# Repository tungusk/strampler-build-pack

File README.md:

# Strämpler Build Pack

Everything you need to **build your own [CTAG Strämpler](https://github.com/ctag-fh-kiel/ctag-straempler)** —
the open-source ESP32 eurorack sample-streaming module — in its compact
**18 HP Antumbra redesign**. Board files in both Eagle *and* KiCad, complete
BOMs with 2026 sourcing fixes, a ready-to-upload fab/assembly package, and
per-kit ordering guides.

## Why this repo exists

The original design files live inside the firmware repo and are in **Eagle
format — a dead tool** (Autodesk sunset Eagle in 2026). The ready-made
panel/PCB sets that used to be sold are delisted. Several key parts of the
2019 BOM have gone EOL. This pack collects the originals, converts them to
a living format, and documents what it actually takes to build one today.

## What's here

| Path | Contents |
|---|---|
| `hardware-eagle/` | The designer's original Eagle 7.3 files: main board + schematic + FR4 panel (untouched) |
| `hardware-kicad/` | **KiCad 10 conversion** — full linked project (schematic + board + symbol lib), converted panel, 3D verification renders, schematic PDF |
| `bom/` | Official Antumbra BOM (Mouser refs), a schematic-derived cross-check BOM, a **Mouser BOM-tool upload file for one kit**, the non-Mouser parts list, and the CTAG RevD reference BOM |
| `assembly-pcbway/` | Ready-to-upload turnkey assembly package: fab BOM, pick-and-place (CPL), order guide, price estimate |
| `KIT-GUIDE.md` | Ordering bare boards + parts as DIY kits, per-kit costs, build order, licensing |
| `KNOB-OPTIONS-20260911.md` | Knob-cap shopping: what is fitted, the panel's 19.27 mm row gap that caps knob diameter, and the Thonk / AliExpress options screened against it |

## 2026 sourcing notes (the important bits)

- **WM8731 codec: obsolete.** Broker stock only (Rochester Electronics for
  genuine EOL parts). The assembly package marks it DNP for hand-soldering.
- **ESP32-WROVER-B: NRND** → use **ESP32-WROVER-IE** (the **-I**/IPEX
  external-antenna variant is required — the module lives behind a metal panel).
- Jacks/pots/SD from [Thonk](https://thonk.co.uk); TFT + antenna from AliExpress.
- Rough costs: **~$160–195/kit** DIY, **~$350–420** for a fab-assembled build.
  Details in `KIT-GUIDE.md` and `assembly-pcbway/PRICE-ESTIMATE.md`.

## Firmware

- Upstream: [ctag-fh-kiel/ctag-straempler](https://github.com/ctag-fh-kiel/ctag-straempler) (GPL 3.0)
- Extended fork with the multi-machine firmware (drum sampler, looper,
  slicer, granular, glitch, Freesound browser, web teleremote):
  [tungusk/ctag-straempler](https://github.com/tungusk/ctag-straempler), branch `v09-machines`
- Flash with `--flash_size detect`; see the firmware repos for build docs.

## Licensing — read before selling anything

- **Hardware: CC BY-NC-SA 4.0** (unchanged from upstream — see `LICENSE.md`).
  Build for yourself, share these files, remix them: all encouraged.
  **Selling boards/kits/modules requires permission** from the rights
  holders (CTAG and Antumbra). Modifications you distribute must carry the
  same license.
- **Firmware: GPL 3.0** — commercial use allowed with source provision.

## Provenance & changes

Original design © 2019 Robert Manzke, Phillip Lamp, Niklas Wantrupp
([CTAG, Kiel UAS](https://www.creative-technologies.de)); PCB redesign by
David Szebenyi ([Antumbra](https://antumbra.eu)). This pack adds (2026-07,
CC BY-NC-SA 4.0): the KiCad 10.0.4 conversion (`kicad-cli pcb import` for the
boards, GUI Eagle-project import for the schematic; auto-matched layers,
KiCad layer names), generated CPL and fab BOMs, the Mouser kit BOM with EOL
substitutions, verification renders/PDF, and the ordering/cost documentation.
Not affiliated with or endorsed by CTAG or Antumbra — errors are ours, not
theirs. Verify footprints against the Eagle originals before fabbing
modified boards.

## Experimental: E-mu-format panel (2026-09)

`panel-emu/` — a 6" × 6" E-mu Modular style front panel for the main board
with 1/4" Switchcraft jacks, bus-normalled CV/trigger inputs, and a ±12 V
regulator sub-board for the E-mu ±15 V bus. Parametric generator + SVG/DXF
cut and art files + README (BOM, wiring, E-mu conventions). One-off for a
hackerspace system; slow burn.

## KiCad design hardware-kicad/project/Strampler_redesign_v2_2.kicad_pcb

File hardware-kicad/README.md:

# Editing the boards (KiCad 10+)

- **Main board + schematic**: open `project/Strampler_redesign_v2_2.kicad_pro`
  — a full linked project (schematic, board, and the Eagle-imported symbol
  library). Footprints are embedded in the board, so it is self-contained.
- **Panel**: open `strampler_panel_v2_2.kicad_pcb` directly in the PCB
  Editor. The artwork is ~34k filled polygons on F.Silkscreen; the copper
  pours are filled zones. It is heavy but edits fine.

After editing, regenerate all fab outputs (gerber zips + centroid) with:

```
./make-fab-files.sh
```

Both gerber sets passed PCBWay audit (2026-07) as generated by that script's
commands.

## Provenance & pitfalls

These files were converted from the Eagle 7.3 originals (`../hardware-eagle/`)
with KiCad 10.0.4. Two importer pitfalls are already fixed here — beware if
you ever re-import from Eagle instead of editing these files:

1. The importer creates **unfilled zones**, which plot as EMPTY gerber
   layers (missing copper, mask and artwork). Fixed by filling copper zones
   and converting non-copper zones to filled `gr_poly` shapes.
2. The importer maps Eagle's t/bRestrict layers to layer `"UNDEFINED"`,
   which KiCad's own parser then refuses to load. The first fix remapped
   them to `User.1` — **which was itself a bug**: `User.1` is not a copper
   layer, so the 1876 tiny restrict rectangles did nothing and the copper
   pours filled straight under the LED light window. The 2026-07 panel run
   came back with a **copper wave** where the original has bare FR4 (found
   2026-08-28 at first-module assembly). **Fixed 2026-08-28:** the 938
   unique rectangles (identical to the F/B.Mask window polygons) were merged
   into one polygon and replaced by a single **keep-out rule area on
   F.Cu + B.Cu** (`copperpour not_allowed`, named "LED light window");
   zones refilled; panel gerbers regenerated. Verified: filled copper ∩
   window = 0 on both layers.

## Main-board audit (2026-08-28) — keep-outs OK, one mask sliver restored

After the panel bug, the main board was checked for the same class of
loss. Eagle's `tRestrict`/`bRestrict` circles (mounting holes of P3 TFT,
jacks, PCB screws) and the `vRestrict` under the crystal all survived as
proper rule areas inside the footprints (`copperpour not_allowed` on
F.Cu/B.Cu; via keep-out on both). Verified with pcbnew: filled copper ∩
every keep-out = 0 (64 pairs). The only dropped item was a 0.15 × 1.3 mm
`tStop` sliver in the `SJ` (solder jumper) package — the mask opening
between SJ1's two pads that makes it bridgeable. Restored as an `fp_rect`
on B.Mask (SJ1 is on the bottom); main gerbers regenerated. The fabbed
2026-07 main boards lack that sliver: SJ1 can still be bridged, it just
takes a blob over the ~0.1 mm mask web. SJ1 joins ESP32 IO19 to TFT
connector pin 9.

## Panel v2_3 (2026-08-29) — M7 pot holes

`strampler_panel_v2_3.kicad_pcb` is the current panel: v2_2 plus the four
CV pot holes and POT1's hole resized 9.2/8.2 → 7.2 mm for M7-bushing pots
(Same Sky PTN091/PTN092 — see build-pack COMPLETION-SHOPPING §POT2–5).
The other 8.2 mm hole is the ENCODER's — deliberately unchanged.
`make-fab-files.sh` builds v2_3; v2_2 is kept as the pre-M7 version
matching the five fabbed (LED-window-defective) panels.

## Refilling zones from the command line

`kicad-cli` has no zone-fill command. After editing a board outside the
GUI (e.g. scripted changes), refill with the bundled Python before
running `make-fab-files.sh`:

```
PY=~/Applications/KiCad/KiCad.app/Contents/Frameworks/Python.framework/Versions/Current/bin/python3
$PY -c "import pcbnew; b=pcbnew.LoadBoard('strampler_panel_v2_2.kicad_pcb'); \
  pcbnew.ZONE_FILLER(b).Fill(b.Zones()); pcbnew.SaveBoard('strampler_panel_v2_2.kicad_pcb', b)"
```

(`SaveBoard` drops a stray `.kicad_pro` next to the panel — delete it.)

Verify against the Eagle originals and the `render-main-*.png` references
before fabbing modified boards. License: CC BY-NC-SA 4.0 (see ../LICENSE.md).

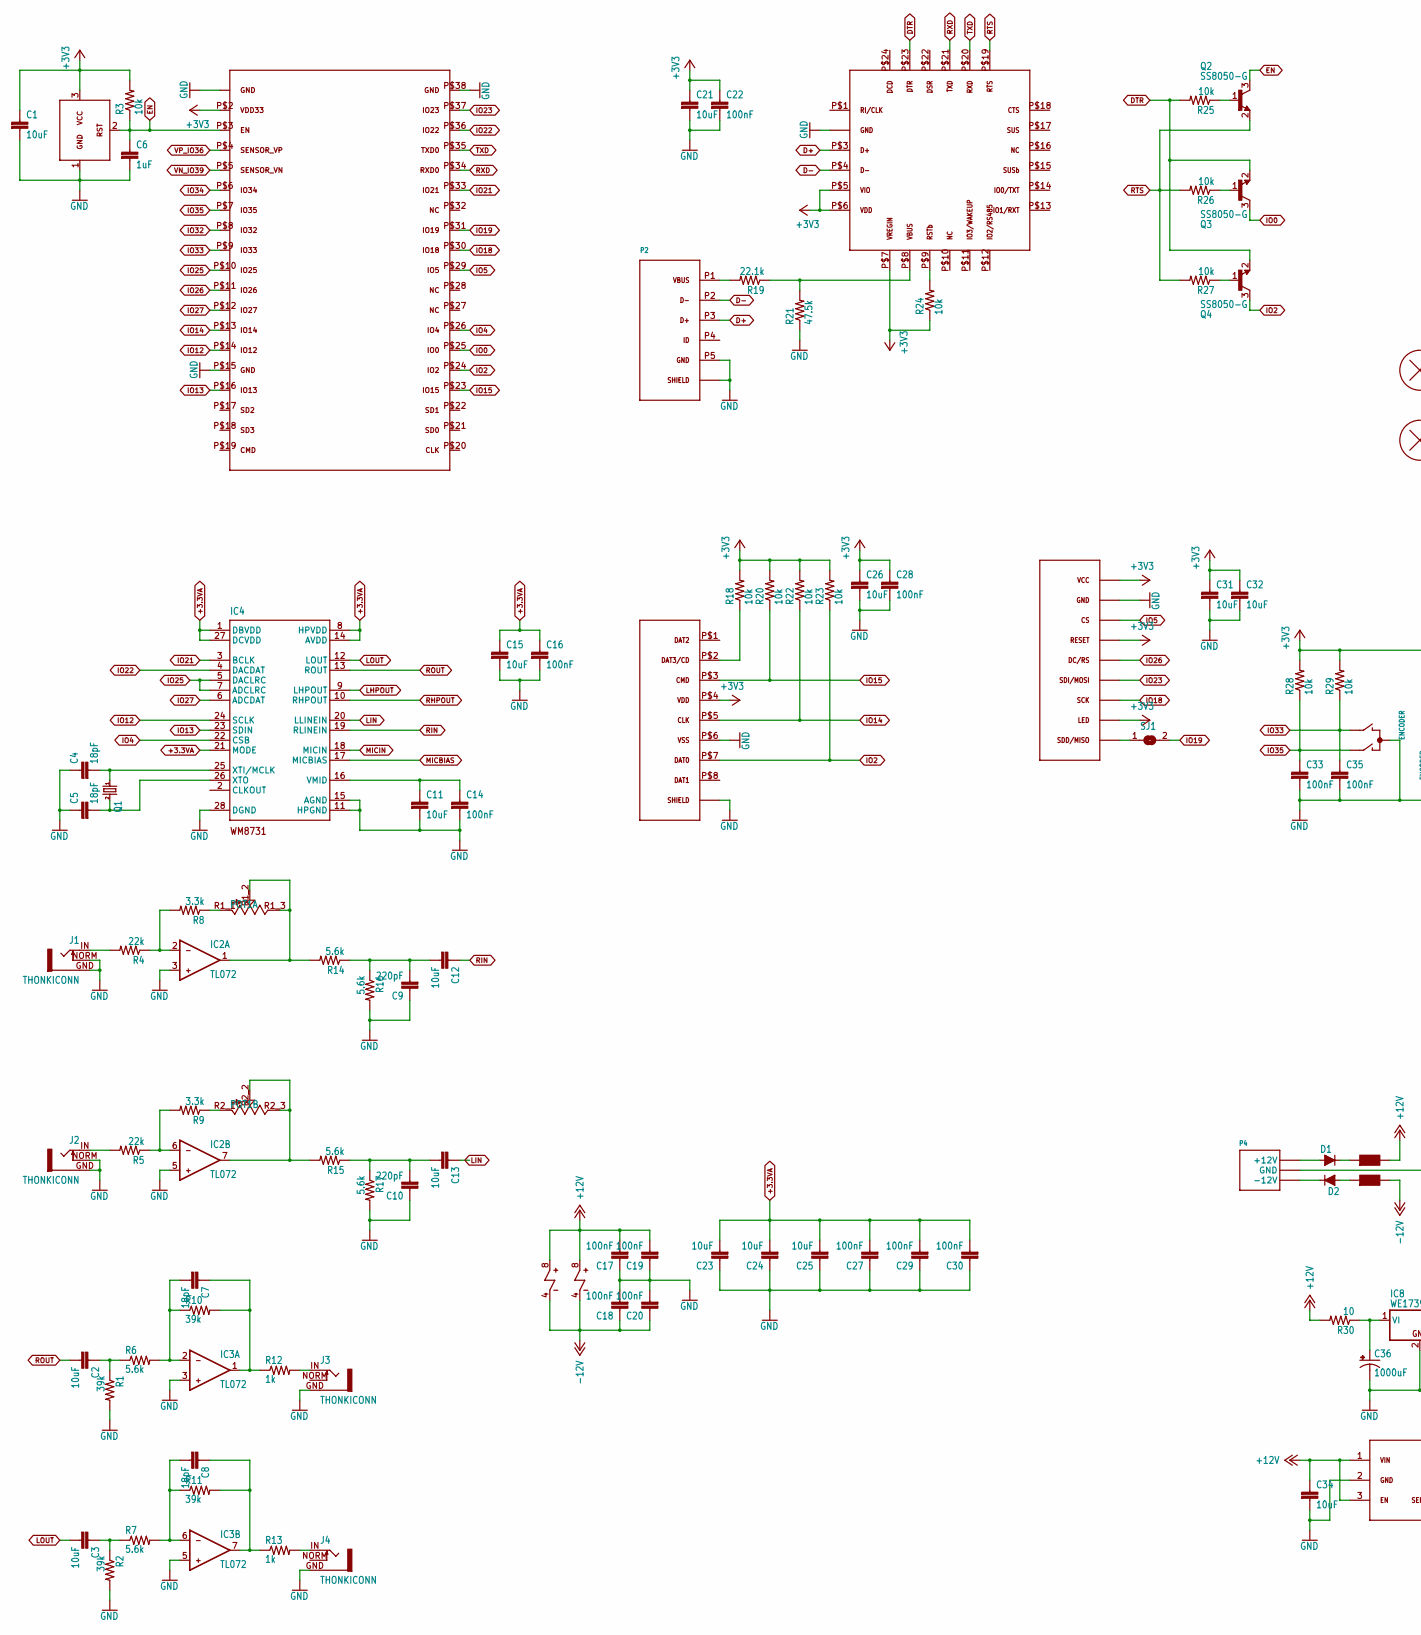
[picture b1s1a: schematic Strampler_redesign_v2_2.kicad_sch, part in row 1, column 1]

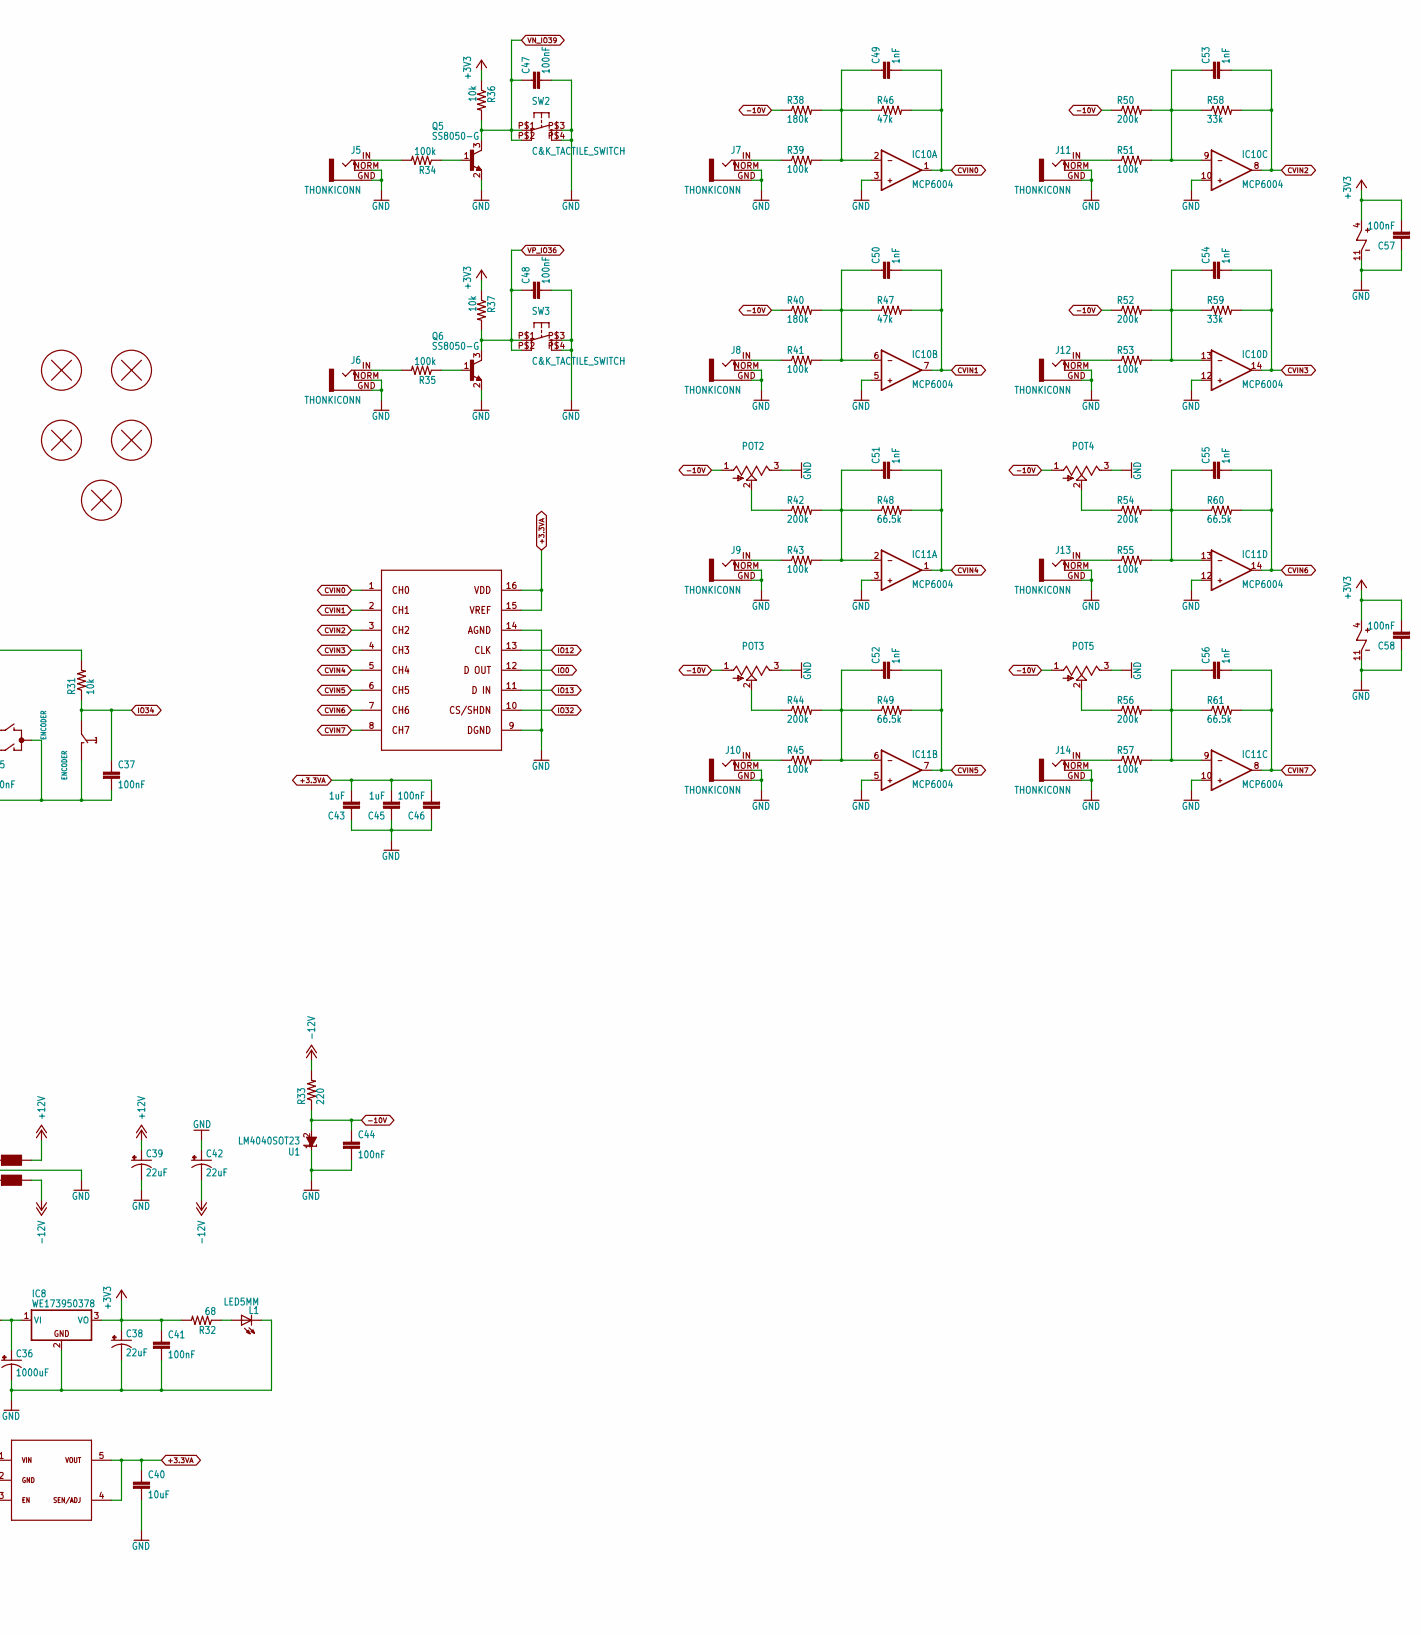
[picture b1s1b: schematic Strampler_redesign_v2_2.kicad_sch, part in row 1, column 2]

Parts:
C1, C2, C3, C11, C12, C13, C15, C21, C23, C24, C25, C26, C31, C32, C40: 10uF; R0805
C4, C5, C7, C8: 18pF; RESISTOR_0603
C6, C43, C45: 1uF; RESISTOR_0603
C9, C10: 220pF; RESISTOR_0603
C14, C16, C17, C18, C19, C20, C22, C27, C28, C29, C30, C33, C35, C37, C41, C44, C46, C47, C48, C57, C58: 100nF; RESISTOR_0603
C34: 10uF; R1210
C36: 1000uF; PANASONIC_G
C38, C39, C42: 22uF; 1206_POL
C49, C50, C51, C52, C53, C54, C55, C56: 1nF; RESISTOR_0603
D1, D2: DIODE; SOD123
F1, F2: FERRITE-BEAD0805; R0805
H1, H2, H3, H4, H5: PCB_SCREW
IC1: MIC803; SOT23
IC2, IC3: TL072; SOIC8
IC4: WM8731; SSOP28
IC5: ESP32-WROVER-B
IC6: CP2102N
IC7: ADP7118; SOT23-5L
IC8: WE173950378; WE78
IC9: MCP3208; SOIC16
IC10, IC11: MCP6004; TSSOP14
J1, J2, J3, J4, J5, J6, J7, J8, J9, J10, J11, J12, J13, J14: THONKICONN; PROTOJACK
L1: LED5MM; LED_5MM
P1: SD-CARD; SD-CARD-THONK
P2: USB-B; USB-B-MOLEX-1050170001
P3: MSP2202_DISPLAY
P4: POWER_SIMPLE10; POWER_10
POT1: POT_DUAL_THONK
POT2, POT3, POT4, POT5: POT_VERTICAL; ALPS_POT_VERTICAL
Q1: CRYSTAL; HC49UP
Q2, Q3, Q4, Q5, Q6: SS8050-G; SOT23
R1, R2, R10, R11: 39k; RESISTOR_0603
R3, R18, R20, R22, R23, R24, R25, R26, R27, R28, R29, R31, R36, R37: 10k; RESISTOR_0603
R4, R5: 22k; RESISTOR_0603
R6, R7, R14, R15, R16, R17: 5.6k; RESISTOR_0603
R8, R9: 3.3k; RESISTOR_0603
R12, R13: 1k; RESISTOR_0603
R19: 22.1k; RESISTOR_0603
R21: 47.5k; RESISTOR_0603
R30: 10; R2512
R32: 68; RESISTOR_0603
R33: 220; RESISTOR_0603
R34, R35, R39, R41, R43, R45, R51, R53, R55, R57: 100k; RESISTOR_0603
R38, R40: 180k; RESISTOR_0603
R42, R44, R50, R52, R54, R56: 200k; RESISTOR_0603
R46, R47: 47k; RESISTOR_0603
R48, R49, R60, R61: 66.5k; RESISTOR_0603
R58, R59: 33k; RESISTOR_0603
SJ1: SJ
SW1: ENCODER; ALPS_EC12E_SW; MPN EC12E2424407
SW2, SW3: C&K_TACTILE_SWITCH
U1: LM4040SOT23; SOT23

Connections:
+3.3VA: C15.1, C16.1, C23.2, C24.2, C25.2, C27.2, C29.2, C30.2, C40.1, C43.2, C45.2, C46.2, IC4.1 (DBVDD), IC4.8 (HPVDD), IC4.14 (AVDD), IC4.21 (MODE), IC4.27 (DCVDD), IC7.4, IC7.5, IC9.15, IC9.16
+3V3: C1.1, C21.1, C22.1, C26.1, C28.1, C31.1, C32.1, C38.2 (+), C41.1, C57.2, C58.2, IC1.3, IC5.P$2, IC6.P$5, IC6.P$6, IC6.P$7, IC8.3 (VO), IC10.4, IC11.4, P1.P$4, P3.LED, P3.LED1, P3.RESET, P3.RESET1, P3.VCC, P3.VCC1, R3.2, R18.2, R20.2, R22.2, R23.2, R24.1, R28.2, R29.2, R31.2, R32.2, R36.1, R37.1
+12V: C17.2, C19.2, C34.1, C39.2 (+), F1.1, IC2.8, IC3.8, IC7.1, IC7.3, R30.2
-10V: C44.1, POT2.1 (A), POT3.1 (A), POT4.1 (A), POT5.1 (A), R33.1, R38.1, R40.1, R50.1, R52.1, U1.2 (A)
-12V: C18.1, C20.1, C42.1 (-), F2.1, IC2.4, IC3.4, R33.2
CVIN0: C49.2, IC9.1, IC10.1, R46.2
CVIN1: C50.2, IC9.2, IC10.7, R47.2
CVIN2: C53.2, IC9.3, IC10.8, R58.2
CVIN3: C54.2, IC9.4, IC10.14, R59.2
CVIN4: C51.2, IC9.5, IC11.1, R48.2
CVIN5: C52.2, IC9.6, IC11.7, R49.2
CVIN6: C55.2, IC9.7, IC11.14, R60.2
CVIN7: C56.2, IC9.8, IC11.8, R61.2
D+: IC6.P$3, P2.P3
D-: IC6.P$4, P2.P2
DTR: IC6.P$23, Q3.2 (E), Q4.2 (E), R25.2
EN: C6.1, IC1.2, IC5.P$3, Q2.3 (C), R3.1
GND: C1.2, C4.1, C5.1, C6.2, C9.1, C10.1, C11.2, C14.2, C15.2, C16.2, C17.1, C18.2, C19.1, C20.2, C21.2, C22.2, C23.1, C24.1, C25.1, C26.2, C27.1, C28.2, C29.1, C30.1, C31.2, C32.2, C33.2, C34.2, C35.2, C36.-, C37.2, C38.1 (-), C39.1 (-), C40.2, C41.2, C42.2 (+), C43.1, C44.2, C45.1, C46.1, C47.2, C48.2, C57.1, C58.1, IC1.1, IC2.3, IC2.5, IC3.3, IC3.5, IC4.11 (HPGND), IC4.15 (AGND), IC4.28 (DGND), IC5.GND, IC5.GND2, IC5.P$1, IC5.P$15, IC5.P$38, IC6.GND, IC6.GND2, IC6.P$2, IC7.2, IC8.2 (GND), IC9.9, IC9.14, IC10.3, IC10.5, IC10.10, IC10.11, IC10.12, IC11.3, IC11.5, IC11.10, IC11.11, IC11.12, J1.GND, J1.NORM, J2.GND, J2.NORM, J3.GND, J4.GND, J5.GND, J5.NORM, J6.GND, J6.NORM, J7.GND, J7.NORM, J8.GND, J8.NORM, J9.GND, J9.NORM, J10.GND, J10.NORM, J11.GND, J11.NORM, J12.GND, J12.NORM, J13.GND, J13.NORM, J14.GND, J14.NORM, L1.K (C), P1.P$6, P1.P$9, P1.P$10, P2.P5, P2.P$1, P2.P$2, P2.P$8, P2.P$9, P2.P$10, P2.P$11, P3.GND, P3.GND1, P4.3 (GND), P4.4 (GND), P4.5 (GND), P4.6 (GND), P4.7 (GND), P4.8 (GND), POT2.3 (B), POT3.3 (B), POT4.3 (B), POT5.3 (B), Q5.2 (E), Q6.2 (E), R1.2, R2.2, R16.2, R17.2, R21.1, SW1.C, SW1.D (1), SW2.P$3 (3), SW2.P$4 (4), SW3.P$3 (3), SW3.P$4 (4), U1.1 (C)
IO0: IC5.P$25, IC9.12, Q3.3 (C)
IO2: IC5.P$24, P1.P$7, Q4.3 (C), R23.1
IO4: IC4.22 (CSB), IC5.P$26
IO5: IC5.P$29, P3.CS, P3.CS1
IO12: IC4.24 (SCLK), IC5.P$14, IC9.13
IO13: IC4.23 (SDIN), IC5.P$16, IC9.11
IO14: IC5.P$13, P1.P$5, R22.1
IO15: IC5.P$23, P1.P$3, R20.1
IO18: IC5.P$30, P3.SCK, P3.SCK1
IO19: IC5.P$31, SJ1.2
IO21: IC4.3 (BCLK), IC5.P$33
IO22: IC4.4 (DACDAT), IC5.P$36
IO23: IC5.P$37, P3.SDI/MOSI, P3.SDI/MOSI1
IO25: IC4.5 (DACLRC), IC4.7 (ADCLRC), IC5.P$10
IO26: IC5.P$11, P3.DC/RS, P3.DC/RS1
IO27: IC4.6 (ADCDAT), IC5.P$12
IO32: IC5.P$8, IC9.10
IO33: C35.1, IC5.P$9, R29.1, SW1.B
IO34: C37.1, IC5.P$6, R31.1, SW1.E (2)
IO35: C33.1, IC5.P$7, R28.1, SW1.A
LHPOUT: IC4.9 (LHPOUT)
LIN: C13.1, IC4.20 (LLINEIN)
LOUT: C3.2, IC4.12 (LOUT)
MICBIAS: IC4.17 (MICBIAS)
MICIN: IC4.18 (MICIN)
unnamed: IC6.P$9, R24.2
unnamed: IC6.P$8, R19.1, R21.2
unnamed: Q2.1 (B), R25.1
unnamed: P2.P1, R19.2
unnamed: P1.P$2, R18.1
unnamed: Q3.1 (B), R26.1
unnamed: P3.SDD/MISO, P3.SDD/MISO1, SJ1.1
unnamed: J5.IN, R34.2
unnamed: Q4.1 (B), R27.1
unnamed: J6.IN, R35.2
unnamed: Q5.1 (B), R34.1
unnamed: Q6.1 (B), R35.1
unnamed: J7.IN, R39.1
unnamed: J11.IN, R51.1
unnamed: C53.1, IC10.9, R50.2, R51.2, R58.1
unnamed: J8.IN, R41.1
unnamed: C49.1, IC10.2, R38.2, R39.2, R46.1
unnamed: POT3.2 (W), R44.1
unnamed: C50.1, IC10.6, R40.2, R41.2, R47.1
unnamed: J12.IN, R53.1
unnamed: C54.1, IC10.13, R52.2, R53.2, R59.1
unnamed: POT2.2 (W), R42.1
unnamed: J9.IN, R43.1
unnamed: C51.1, IC11.2, R42.2, R43.2, R48.1
unnamed: J13.IN, R55.1
unnamed: C55.1, IC11.13, R54.2, R55.2, R60.1
unnamed: J10.IN, R45.1
unnamed: C52.1, IC11.6, R44.2, R45.2, R49.1
unnamed: J14.IN, R57.1
unnamed: C56.1, IC11.9, R56.2, R57.2, R61.1
unnamed: J1.IN, R4.2
unnamed: IC2.2, R4.1, R8.2
unnamed: D1.+, P4.9 (+12V), P4.10 (+12V)
unnamed: POT1.R1_1 (A), R8.1
unnamed: POT5.2 (W), R56.1
unnamed: IC2.1, POT1.R1_2 (W), POT1.R1_3 (B), R14.2
unnamed: C9.2, C12.2, R14.1, R16.1
unnamed: POT4.2 (W), R54.1
unnamed: J2.IN, R5.2
unnamed: IC2.6, R5.1, R9.2
unnamed: POT1.R2_1 (A), R9.1
unnamed: IC2.7, POT1.R2_2 (W), POT1.R2_3 (B), R15.2
unnamed: C5.2, IC4.26 (XTO), Q1.2
unnamed: C4.2, IC4.25 (XTI/MCLK), Q1.1
unnamed: C10.2, C13.2, R15.1, R17.1
unnamed: C7.1, IC3.1, R10.2, R12.1
unnamed: D1.-, F1.2
unnamed: C7.2, IC3.2, R6.2, R10.1
unnamed: C2.1, R1.1, R6.1
unnamed: C36.+, IC8.1 (VI), R30.1
unnamed: J3.IN, R12.2
unnamed: D2.-, P4.1 (-12V), P4.2 (-12V)
unnamed: C8.1, IC3.7, R11.2, R13.1
unnamed: C8.2, IC3.6, R7.2, R11.1
unnamed: C11.1, C14.1, IC4.16 (VMID)
unnamed: C3.1, R2.1, R7.1
unnamed: J4.IN, R13.2
unnamed: D2.+, F2.2
unnamed: L1.A, R32.1
RHPOUT: IC4.10 (RHPOUT)
RIN: C12.1, IC4.19 (RLINEIN)
ROUT: C2.2, IC4.13 (ROUT)
RTS: IC6.P$19, Q2.2 (E), R26.2, R27.2
RXD: IC5.P$34, IC6.P$21
TXD: IC5.P$35, IC6.P$20
VN_IO39: C47.1, IC5.P$5, Q5.3 (C), R36.2, SW2.P$1 (1), SW2.P$2 (2)
VP_IO36: C48.1, IC5.P$4, Q6.3 (C), R37.2, SW3.P$1 (1), SW3.P$2 (2)

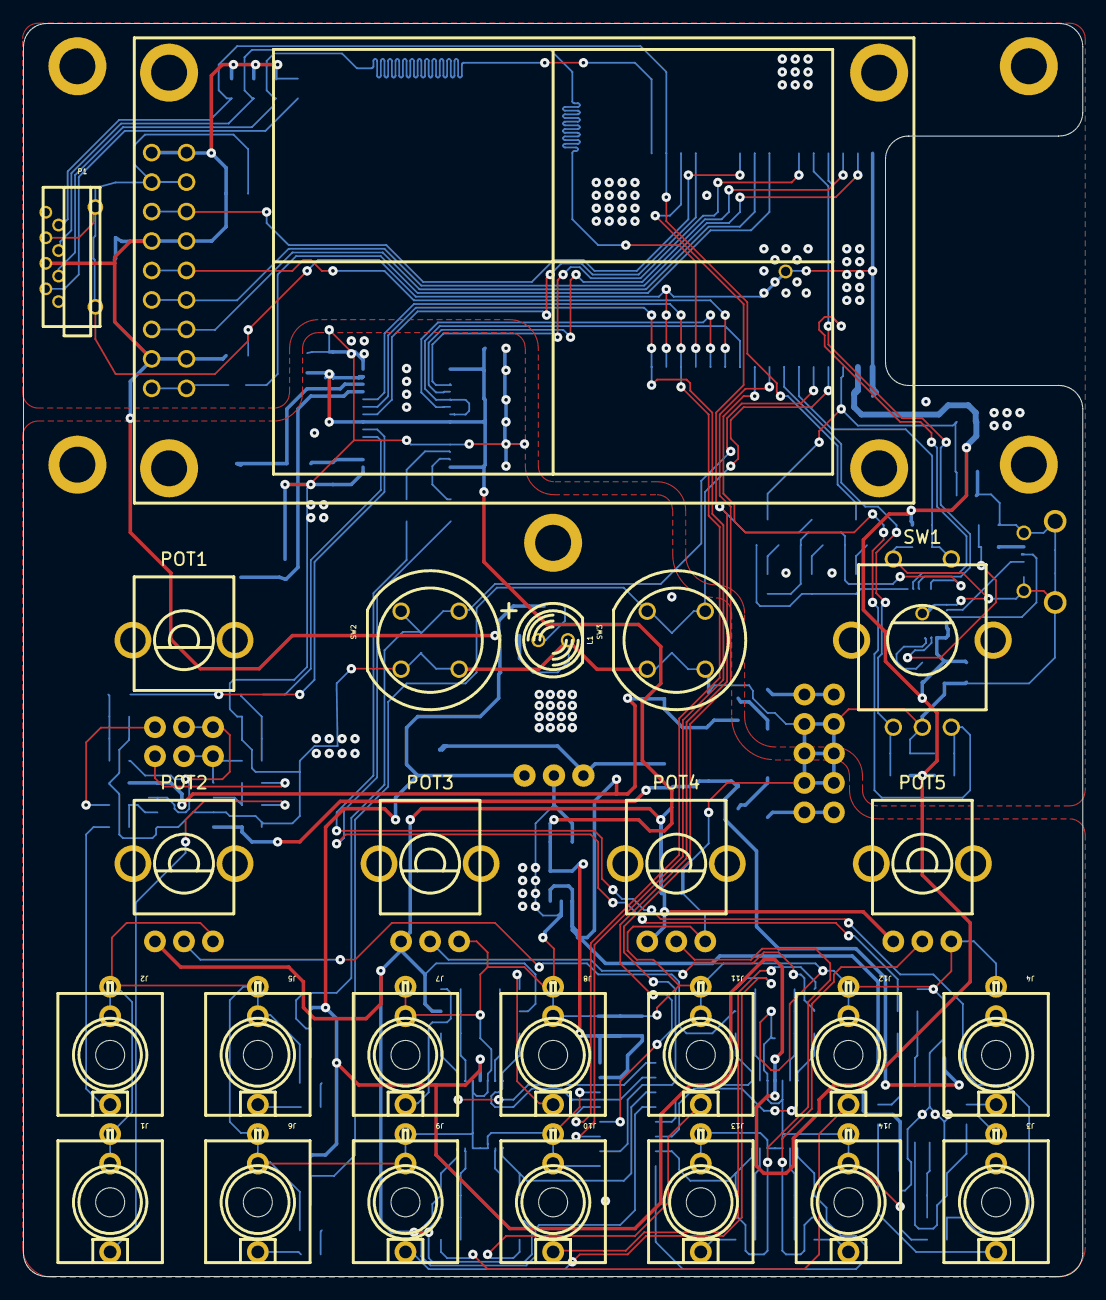
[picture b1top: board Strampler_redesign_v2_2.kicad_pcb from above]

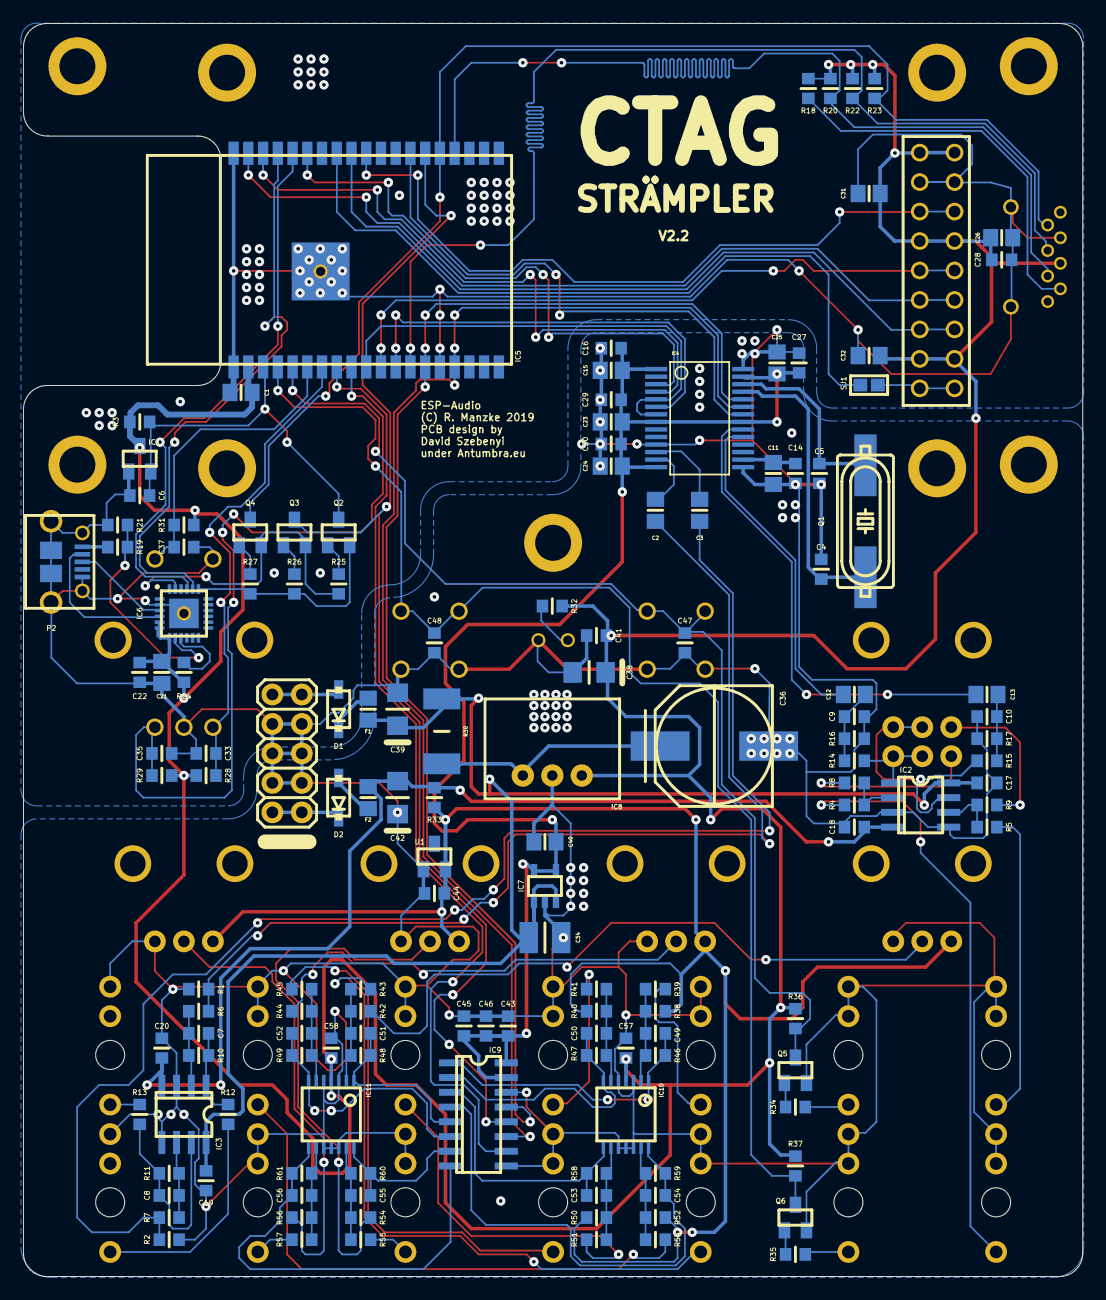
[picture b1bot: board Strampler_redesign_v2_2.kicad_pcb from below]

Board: 2 copper layers, 91.3 x 108.0 mm, 174 parts (144 on the bottom side), 106 nets.

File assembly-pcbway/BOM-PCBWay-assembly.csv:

Designator,Qty,Description,Package,Mfg Part Number,Supplier,Supplier Part Number,Type,Notes
R30,1,Resistor 10,2512,,Mouser,279-CRGP2512F10R,SMD,
R32,1,"Resistor, 1% 68",0603,,Mouser,603-AC0603FR-0768RL,SMD,
R33,1,"Resistor, 1% 220",0603,,Mouser,652-CR0603FX-2200ELF,SMD,
R12 R13,2,"Resistor, 1% 1k",0603,,Mouser,652-CR0603FX-1001ELF,SMD,
R8 R9,2,"Resistor, 1% 3.3k",0603,,Mouser,652-CR0603-FX3301ELF,SMD,
R6 R7 R14 R15 R16 R17,6,"Resistor, 1% 5.6k",0603,,Mouser,652-CR0603FX-5601ELF,SMD,
R3 R18 R20 R22 R23 R24 R25 R26 R27 R28 R29 R31 R36 R37,14,"Resistor, 1% 10k",0603,,Mouser,652-CR0603FX-1002ELF,SMD,
R4 R5,2,"Resistor, 1% 22k",0603,,Mouser,652-CR0603FX-2202ELF,SMD,
R19,1,"Resistor, 1% 22.1k",0603,,Mouser,652-CR0603FX-2212ELF,SMD,
R58 R59,2,"Resistor, 1% 33k",0603,,Mouser,652-CR0603FX-3302ELF,SMD,
R1 R2 R10 R11,4,"Resistor, 1% 39k",0603,,Mouser,652-CR0603FX-3902ELF,SMD,
R46 R47,2,"Resistor, 1% 47k",0603,,Mouser,652-CR0603FX-4702ELF,SMD,
R21,1,"Resistor, 1% 47.5k",0603,,Mouser,603-RC0603FR-0747K5L,SMD,
R48 R49 R60 R61,4,"Resistor, 1% 66.5k",0603,,Mouser,652-CR0603-FX6652ELF,SMD,
R34 R35 R39 R41 R43 R45 R51 R53 R55 R57,10,"Resistor, 1% 100k",0603,,Mouser,603-RC0603FR-07100KL,SMD,
R38 R40,2,"Resistor, 1% 180k",0603,,Mouser,652-CR0603FX-1803ELF,SMD,
R42 R44 R50 R52 R54 R56,6,"Resistor, 1% 200k",0603,,Mouser,652-CR0603FX-2003ELF,SMD,
C4 C5 C7 C8,4,"Capacitor, ceramic 18pF",0603,,Mouser,80-C0603C180J5G,SMD,
C9 C10,2,"Capacitor, ceramic 220pF",0603,,Mouser,710-885012206055,SMD,
C49 C50 C51 C52 C53 C54 C55 C56,8,"Capacitor, ceramic 1nF",0603,,Mouser,77-VJ0603Y102KXQCBC,SMD,
C14 C16 C17 C18 C19 C20 C22 C27 C28 C29 C30 C33 C35 C37 C41 C44 C46 C47 C48 C57 C58,21,"Capacitor, ceramic 100nF",0603,,Mouser,80-C0603X104K5R,SMD,
C6 C43 C45,3,"Capacitor, ceramic 1uF",0603,,Mouser,603-CC603KRX7R7BB105,SMD,
C1 C2 C3 C11 C12 C13 C15 C21 C23 C24 C25 C26 C31 C32 C40,15,"Capacitor, ceramic 10uF",0805,,Mouser,81-GRM21BR70J106KA3L,SMD,
C38 C39 C42,3,"Capacitor, tantalum, polarized 22uF",1206,,Mouser,755-TCTAL1C226M8R,SMD,
C34,1,"Capacitor, ceramic 10uF",1210,,Mouser,710-885012209005,SMD,
C36,1,"Capacitor, electrolytic 1000uF",Panasonic G,,Mouser,661-APXG160A102MJA0G,SMD,
F1 F2,2,Ferrite bead,0805,,Mouser,623-2508056017Y2,SMD,
D1 D2,2,STPS2L40ZFY diode,SOD-123,,Mouser,511-STPS2L40ZFY,SMD,
Q1,1,Crystal 11.2896MHz,HC49UP,,Mouser,815-ABLS211.2896B4YT,SMD,
IC7,1,ADP7118,SOT23-5,,Mouser,584-ADP7118AUJZ3.3R7,SMD,
IC6,1,CP2102N,CP2102N,,Mouser,634-CP2102NA02GQFN24,SMD,
IC5,1,ESP32-WROVER-IE (8MB flash/8MB PSRAM),,ESP32-WROVER-IE-N8R8,,,SMD,substitute for discontinued WROVER-IB; IPEX antenna variant REQUIRED
U1,1,LM4040 Shunt Vref 10V,SOT23,,Mouser,595-LM4040B10IDBZR,SMD,
IC9,1,MCP3208,SOIC16,,Mouser,579-MCP3208T-CI/SL,SMD,
IC10 IC11,2,MCP6004 Quad Opamp,TSSOP14,,Mouser,579-MCP6004-I/ST,SMD,
IC1,1,MIC803,SOT23,,Mouser,998-MIC803-31D3VM3TR,SMD,
Q2 Q3 Q4 Q5 Q6,5,SS8050-G,SOT23,,Mouser,750-SS8050-G,SMD,
IC2 IC3,2,TL072 Dual Opamp,SOIC8,,Mouser,595-TL072IDR,SMD,
IC8,1,WE173950378,WE78,,Mouser,919-R-78E3.3-1.0,SMD,
IC4,1,WM8731,SSOP28,WM8731SEDS/V,Mouser,238-WM8731SEDS/V,SMD,"DO NOT POPULATE - obsolete part, customer will hand-solder"
